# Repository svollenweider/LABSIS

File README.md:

# LABSIS - WIP
Laboratory Monitoring System using an Arduino Nano 33 Iot. It records Temperature, Pressure, Humidity and Magnetic field. In addition it has connections to attach a 10kOhm thermistor, a flowmeter and a flood sensor as well as relays. 

# Arduino Library Prerequisites
- Adafruit BME280
- Adafruit MCP9808
- Dependencies of Adafruit BME280 and MCP9808
- Library for ALS31300.h (included)
- WiFiNINA
- RTCZero

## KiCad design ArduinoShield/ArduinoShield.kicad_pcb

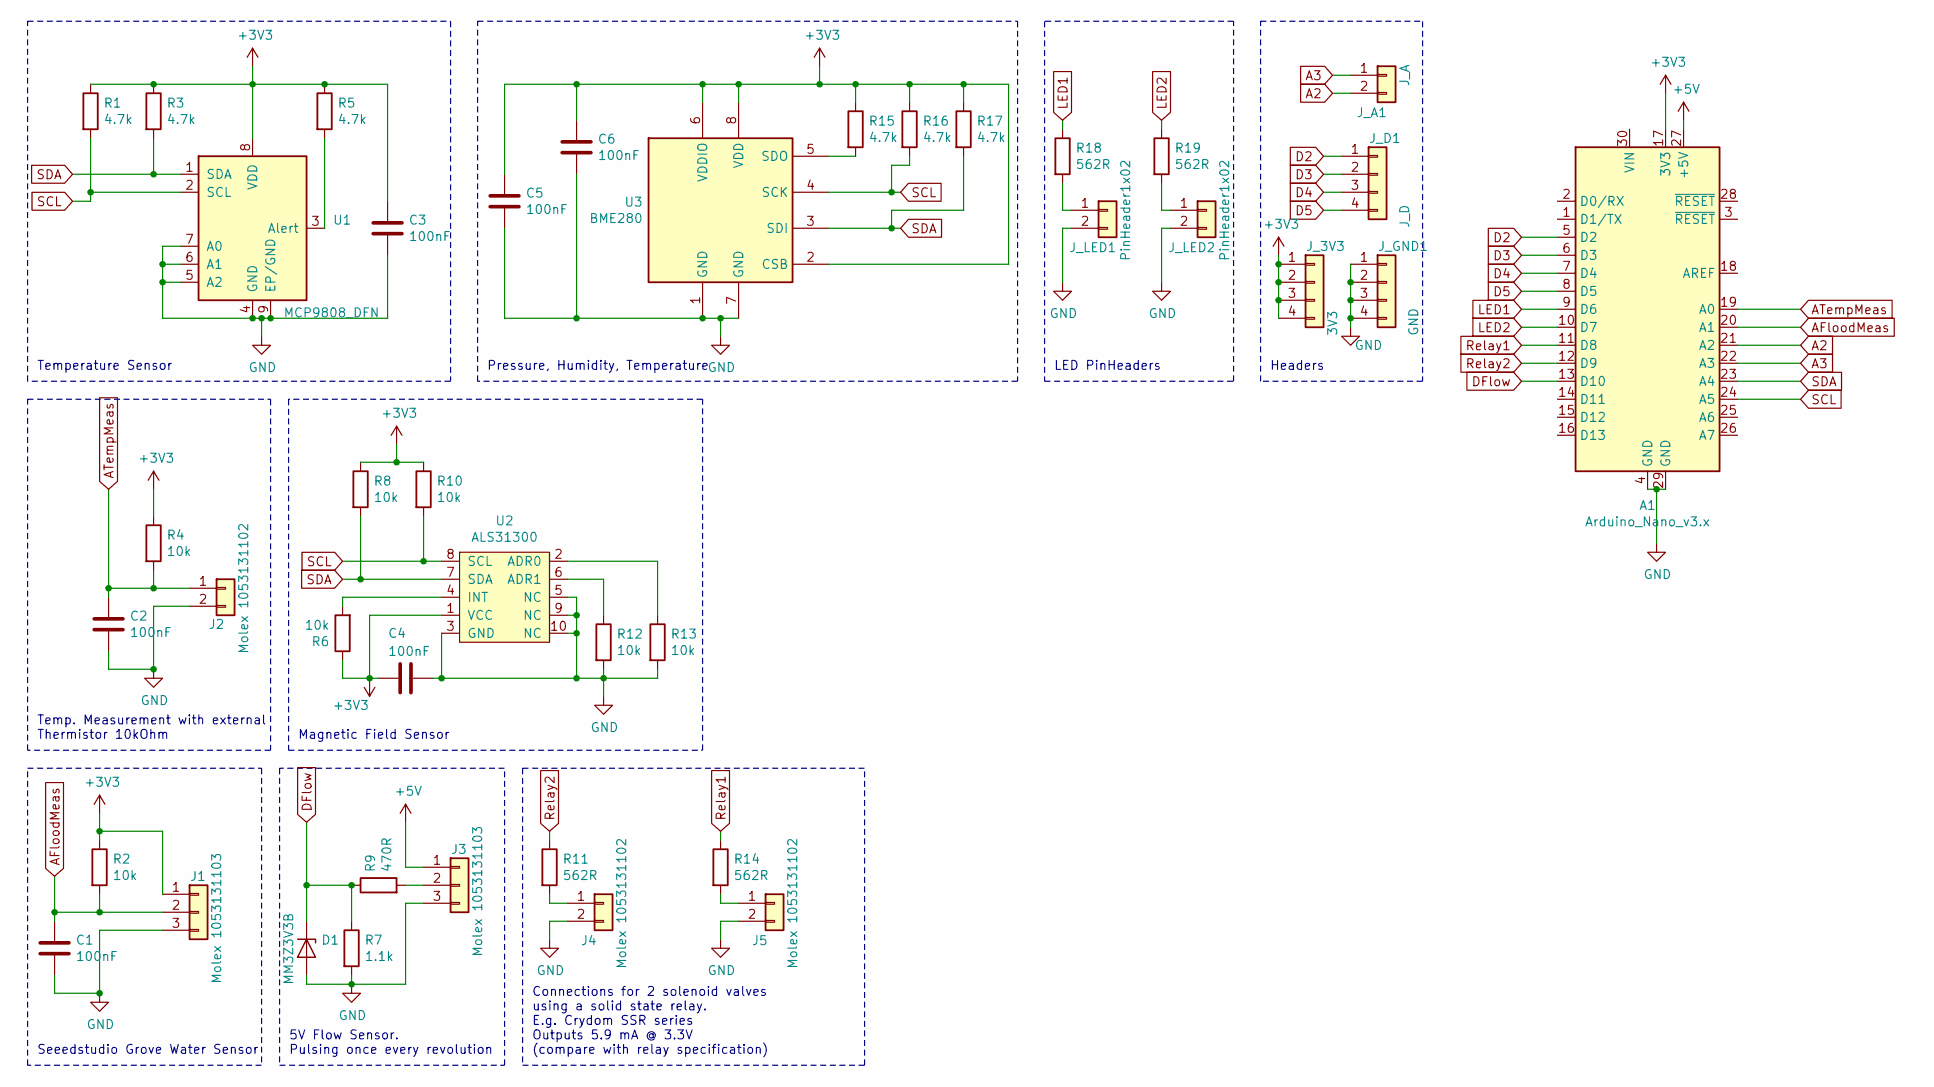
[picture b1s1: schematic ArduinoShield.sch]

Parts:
A1: Arduino_Nano_v3.x; Arduino_Nano
C1, C2, C3, C4, C5, C6: 100nF; C_0201_0603Metric
D1: MM3Z3V3B; D_SOD-323F
J1, J3: Molex 1053131103; Molex_Nano-Fit_105313-xx03_1x03_P2.50mm_Horizontal
J2, J4, J5: Molex 1053131102; Molex_Nano-Fit_105313-xx02_1x02_P2.50mm_Horizontal
J_3V3: 3V3; PinHeader_1x04_P2.54mm_Vertical
J_A1: J_A; PinHeader_1x02_P2.54mm_Vertical
J_D1: J_D; PinHeader_1x04_P2.54mm_Vertical
J_GND1: GND; PinHeader_1x04_P2.54mm_Vertical
J_LED1, J_LED2: PinHeader1x02; PinHeader_1x02_P2.54mm_Vertical
R1, R3, R5, R15, R16, R17: 4.7k; R_0201_0603Metric
R2, R4, R6, R8, R10, R12, R13: 10k; R_0201_0603Metric
R7: 1.1k; R_0201_0603Metric
R9: 470R; R_0201_0603Metric
R11, R14, R18, R19: 562R; R_0201_0603Metric
U1: MCP9808_DFN
U2: ALS31300; DFN-10-1EP_3x3mm_P0.5mm_EP1.55x2.48mm
U3: BME280; Bosch_LGA-8_2.5x2.5mm_P0.65mm_ClockwisePinNumbering

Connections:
+3V3: A1.17 (3V3), C3.1, C4.2, C5.1, C6.1, J1.1, J_3V3.1, J_3V3.2, J_3V3.3, J_3V3.4, R1.1, R2.1, R3.1, R4.1, R5.1, R6.1, R8.1, R10.1, R15.1, R16.1, R17.1, U1.8 (VDD), U2.1 (VCC), U3.2 (CSB), U3.6 (VDDIO), U3.8 (VDD)
+5V: A1.27 (+5V), J3.1
A2: A1.21 (A2), J_A1.2
A3: A1.22 (A3), J_A1.1
AFloodMeas: A1.20 (A1), C1.1, J1.2, R2.2
ATempMeas: A1.19 (A0), C2.1, J2.1, R4.2
D2: A1.5 (D2), J_D1.1
D3: A1.6 (D3), J_D1.2
D4: A1.7 (D4), J_D1.3
D5: A1.8 (D5), J_D1.4
DFlow: A1.13 (D10), D1.1 (K), R7.1, R9.1
GND: A1.4 (GND), A1.29 (GND), C1.2, C2.2, C3.2, C4.1, C5.2, C6.2, D1.2 (A), J1.3, J2.2, J3.3, J4.2, J5.2, J_GND1.1, J_GND1.2, J_GND1.3, J_GND1.4, J_LED1.2, J_LED2.2, R7.2, R12.2, R13.2, U1.4 (GND), U1.5 (A2), U1.6 (A1), U1.7 (A0), U1.9 (EP/GND), U2.3 (GND), U2.5 (NC), U2.9 (NC), U2.10 (NC), U3.1 (GND), U3.7 (GND)
LED1: A1.9 (D6), R18.1
LED2: A1.10 (D7), R19.1
unnamed: J3.2, R9.2
unnamed: J4.1, R11.2
unnamed: J5.1, R14.2
unnamed: J_LED1.1, R18.2
unnamed: J_LED2.1, R19.2
unnamed: R5.2, U1.3 (Alert)
unnamed: R6.2, U2.4 (INT)
unnamed: R12.1, U2.6 (ADR1)
unnamed: R13.1, U2.2 (ADR0)
unnamed: R15.2, U3.5 (SDO)
Relay1: A1.11 (D8), R14.1
Relay2: A1.12 (D9), R11.1
SCL: A1.24 (A5), R1.2, R10.2, R16.2, U1.2 (SCL), U2.8 (SCL), U3.4 (SCK)
SDA: A1.23 (A4), R3.2, R8.2, R17.2, U1.1 (SDA), U2.7 (SDA), U3.3 (SDI)

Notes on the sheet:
Temperature Sensor
Pressure, Humidity, Temperature
Temp. Measurement with external Thermistor 10kOhm
Magnetic Field Sensor
Seeedstudio Grove Water Sensor
5V Flow Sensor. Pulsing once every revolution
Connections for 2 solenoid valves using a solid state relay. E.g. Crydom SSR series Outputs 5.9 mA @ 3.3V (compare with relay specification)
LED PinHeaders
Headers

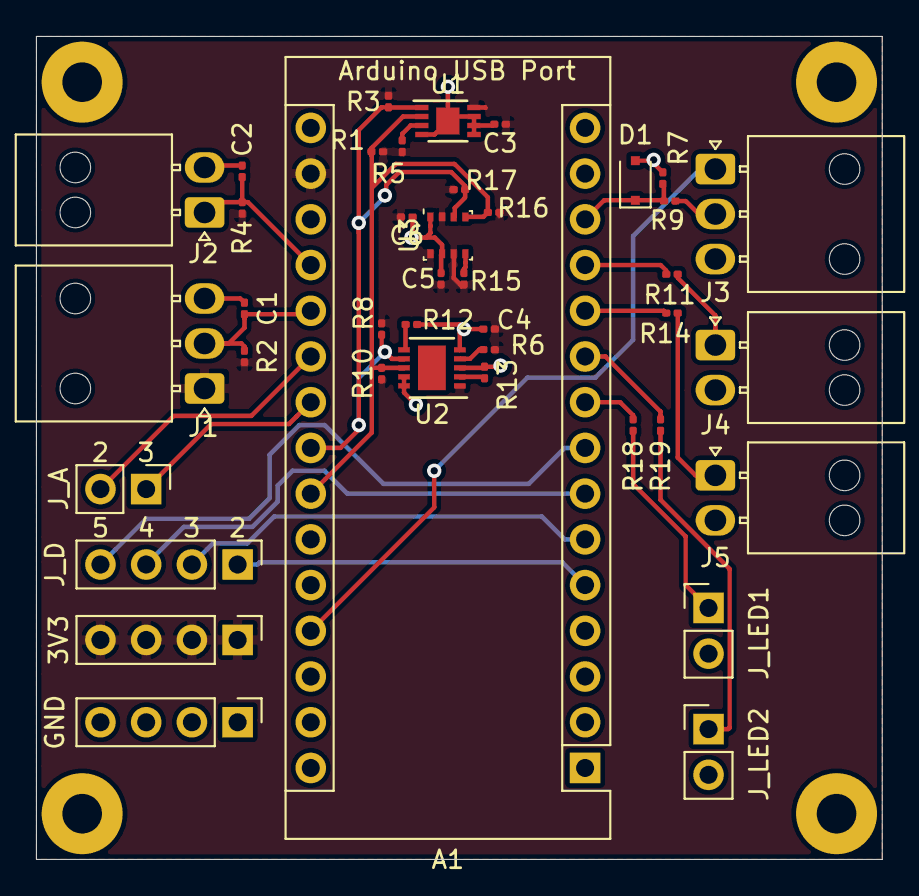
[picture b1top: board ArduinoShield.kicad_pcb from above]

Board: 2 copper layers, 47.0 x 45.7 mm, 41 parts (0 on the bottom side), 28 nets.

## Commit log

2020-03-23 Moved Files to programming folder
2020-03-23 Added Schematics and PCB
2020-03-23 Renamed folder
2020-03-23 Modified Library
2020-03-23 Added DataObject to store Data in
2020-03-23 Started with initialization
2020-03-23 Added Accelerometer
2020-03-24 Moved files, added NetworkSettings_example, added DataBaseConnection abstract class
2020-03-24 Changed Names
2020-03-25 Added the libraries for the Shield
2020-03-25 Added include guards fixed include errors
2020-03-25 Fixed missing endif
2020-03-30 Small changes to design, added BOM
2020-03-31 Changed .gitignore
2020-03-31 Updated gitignore
2020-03-31 Updated gitignore, fixed bugs in connection
2020-03-31 Another Gitgnore update
2020-03-31 InfluxDB connection working now
2020-03-31 Removed backup files
2020-04-08 Completed BOM
2020-04-08 Added Gerber File
2020-04-08 Fixed BOM, added Gerber File export
2020-04-14 Updated Hole size for Arduino, Created Footprint for bigger hole sizes
2020-05-15 Modified part that was wrong in KiCad Library (MCP9808)
2020-05-15 Fixed merging issues
2020-05-15 Final Fix for pcb
2020-05-20 Added Comments
